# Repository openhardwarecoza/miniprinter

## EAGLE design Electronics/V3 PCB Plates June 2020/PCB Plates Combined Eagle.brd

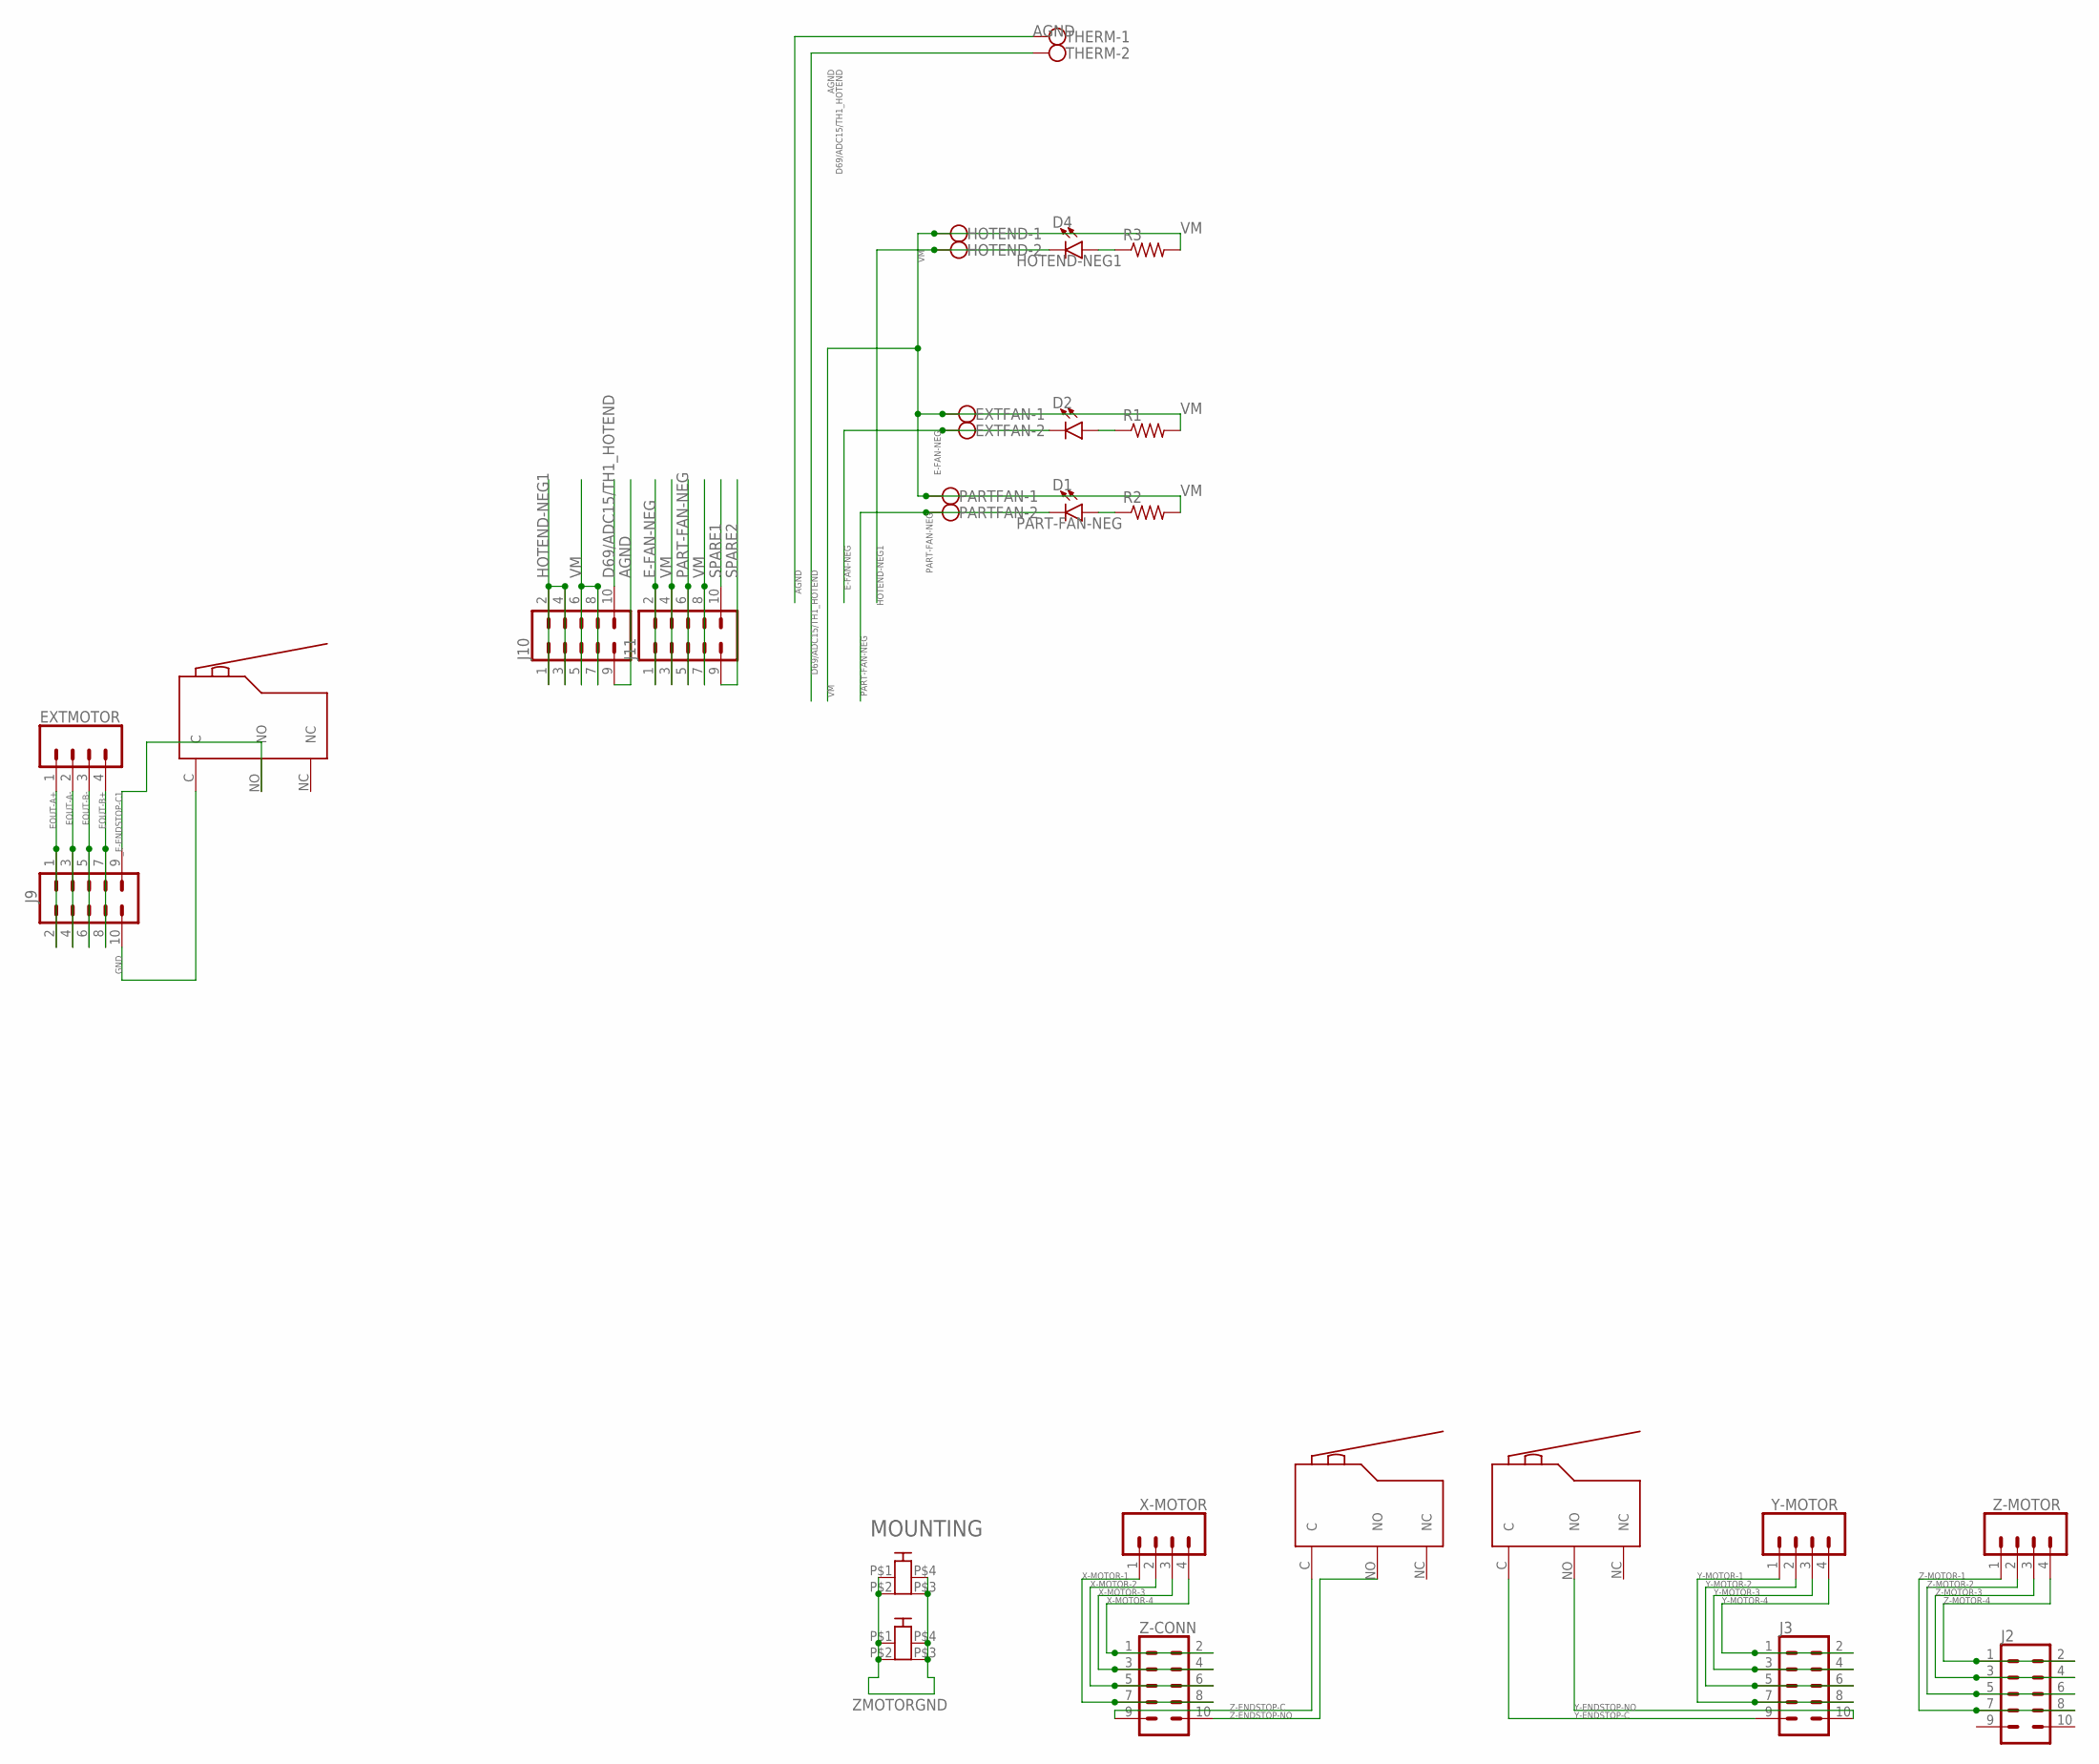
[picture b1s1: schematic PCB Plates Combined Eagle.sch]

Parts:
CON1, CON7: PCB-2M3; PCB2-M3
D1, D2, D4: LED-FKIT-1206; FKIT-LED-1206
EXTFAN: W237-102
EXTMOTOR: CONN_04SCREW_LOCK; SCREWTERMINAL-3.5MM-4_LOCK
HOTEND: W237-102
J2, J3, J9, J10, J11: CONN_05X2SHD_LOCK; 2X5-SHROUDED_LOCK
PARTFAN: W237-102
R1, R2, R3: R-US_R1206; R1206
THERM: W237-102
U$1: Lever Microswitch Leftangle PCB mount, with Rolle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; LEVERMICROPCB-LEFTANGLE
X-MOTOR: CONN_04SCREW_LOCK; SCREWTERMINAL-3.5MM-4_LOCK
XENDSTOP: Lever Microswitch Leftangle PCB mount, with Rolle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; LEVERMICROPCB-LEFTANGLE
Y-MOTOR: CONN_04SCREW_LOCK; SCREWTERMINAL-3.5MM-4_LOCK
Z-CONN: CONN_05X2SHD_LOCK; 2X5-SHROUDED_LOCK
Z-MOTOR: CONN_04SCREW_LOCK; SCREWTERMINAL-3.5MM-4_LOCK
ZENDSTOP: Lever Microswitch Leftangle PCB mount, with Rolle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; LEVERMICROPCB-LEFTANGLE

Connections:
AGND: J10.9, THERM.1
D69/ADC15/TH1_HOTEND: J10.10, THERM.2
E-FAN-NEG: D2.C, EXTFAN.2, J11.1, J11.2
EOUT-A+: EXTMOTOR.1, J9.1, J9.2
EOUT-A-: EXTMOTOR.2, J9.3, J9.4
EOUT-B+: EXTMOTOR.4, J9.7, J9.8
EOUT-B-: EXTMOTOR.3, J9.5, J9.6
GND: J9.10, XENDSTOP.C
HOTEND-NEG1: D4.C, HOTEND.2, J10.1, J10.2, J10.3, J10.4
unnamed: D2.A, R1.1
unnamed: D1.A, R2.1
unnamed: D4.A, R3.1
PART-FAN-NEG: D1.C, J11.5, J11.6, PARTFAN.2
SPARE1: J11.10
SPARE2: J11.9
VM: EXTFAN.1, HOTEND.1, J10.5, J10.6, J10.7, J10.8, J11.3, J11.4, J11.7, J11.8, PARTFAN.1, R1.2, R2.2, R3.2
X-MOTOR-1: X-MOTOR.1, Z-CONN.7, Z-CONN.8
X-MOTOR-2: X-MOTOR.2, Z-CONN.5, Z-CONN.6
X-MOTOR-3: X-MOTOR.3, Z-CONN.3, Z-CONN.4
X-MOTOR-4: X-MOTOR.4, Z-CONN.1, Z-CONN.2
Y-ENDSTOP-C: J3.9, U$1.C
Y-ENDSTOP-NO: J3.10, U$1.NO
Y-MOTOR-1: J3.7, J3.8, Y-MOTOR.1
Y-MOTOR-2: J3.5, J3.6, Y-MOTOR.2
Y-MOTOR-3: J3.3, J3.4, Y-MOTOR.3
Y-MOTOR-4: J3.1, J3.2, Y-MOTOR.4
Z-ENDSTOP-C: Z-CONN.9, ZENDSTOP.C
Z-ENDSTOP-NO: Z-CONN.10, ZENDSTOP.NO
Z-MOTOR-1: J2.7, J2.8, Z-MOTOR.1
Z-MOTOR-2: J2.5, J2.6, Z-MOTOR.2
Z-MOTOR-3: J2.3, J2.4, Z-MOTOR.3
Z-MOTOR-4: J2.1, J2.2, Z-MOTOR.4
ZMOTORGND: CON1.P$1, CON1.P$2, CON1.P$3, CON1.P$4, CON7.P$1, CON7.P$2, CON7.P$3, CON7.P$4
_E-ENDSTOP-C1: J9.9, XENDSTOP.NO

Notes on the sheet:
MOUNTING

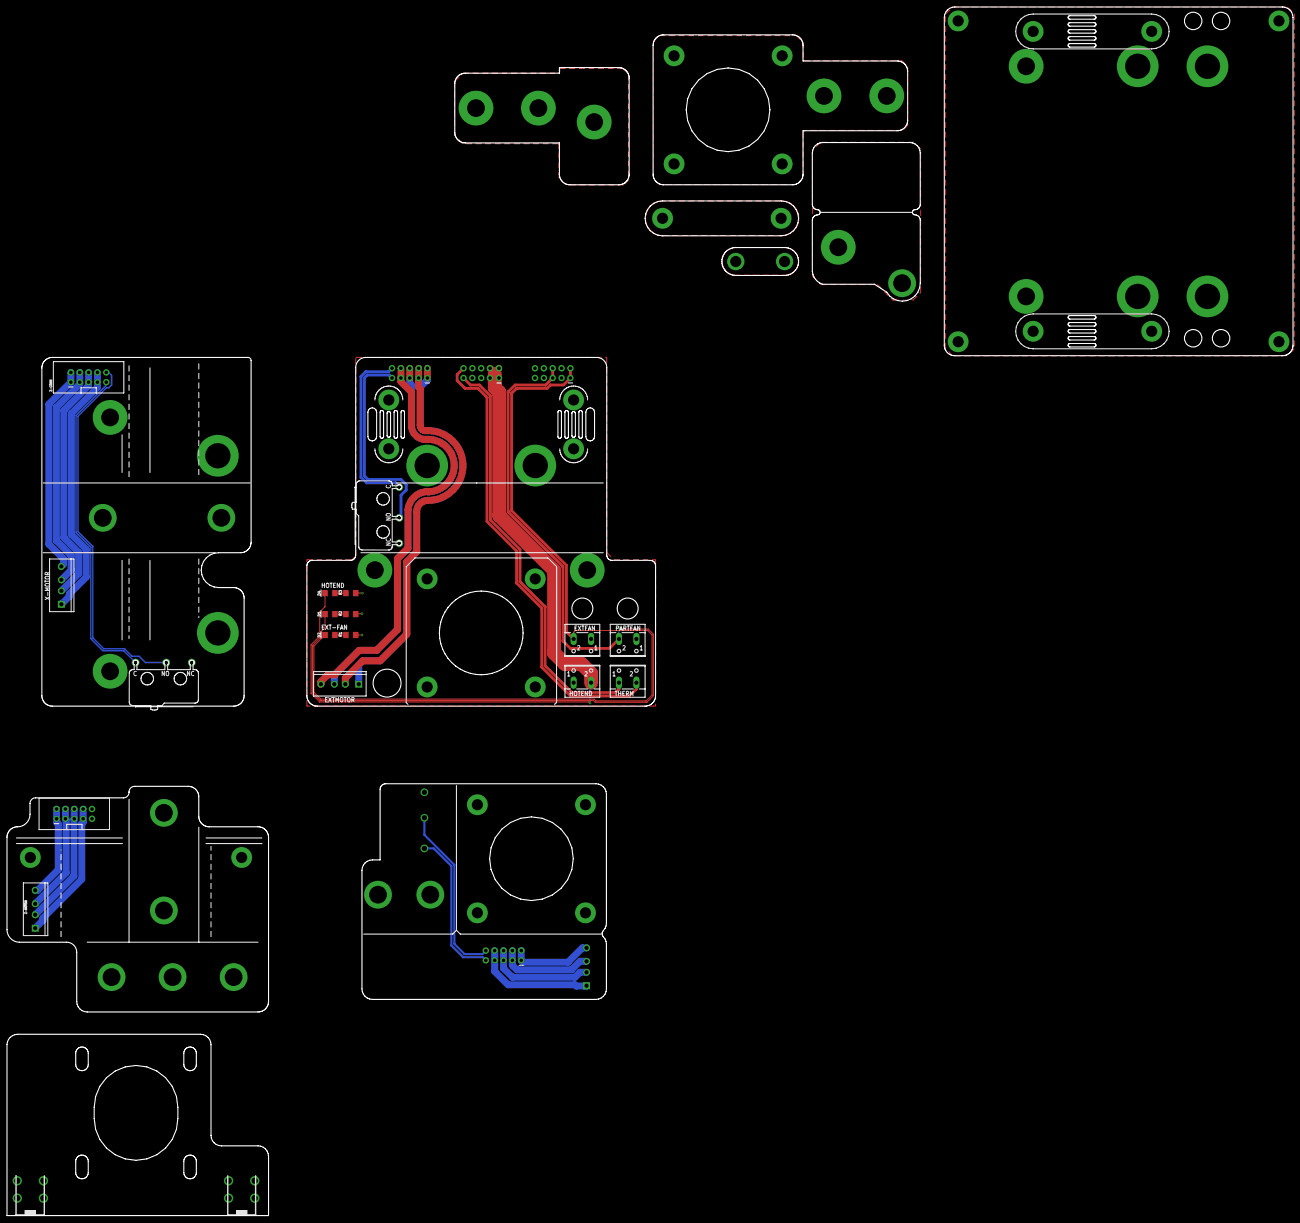
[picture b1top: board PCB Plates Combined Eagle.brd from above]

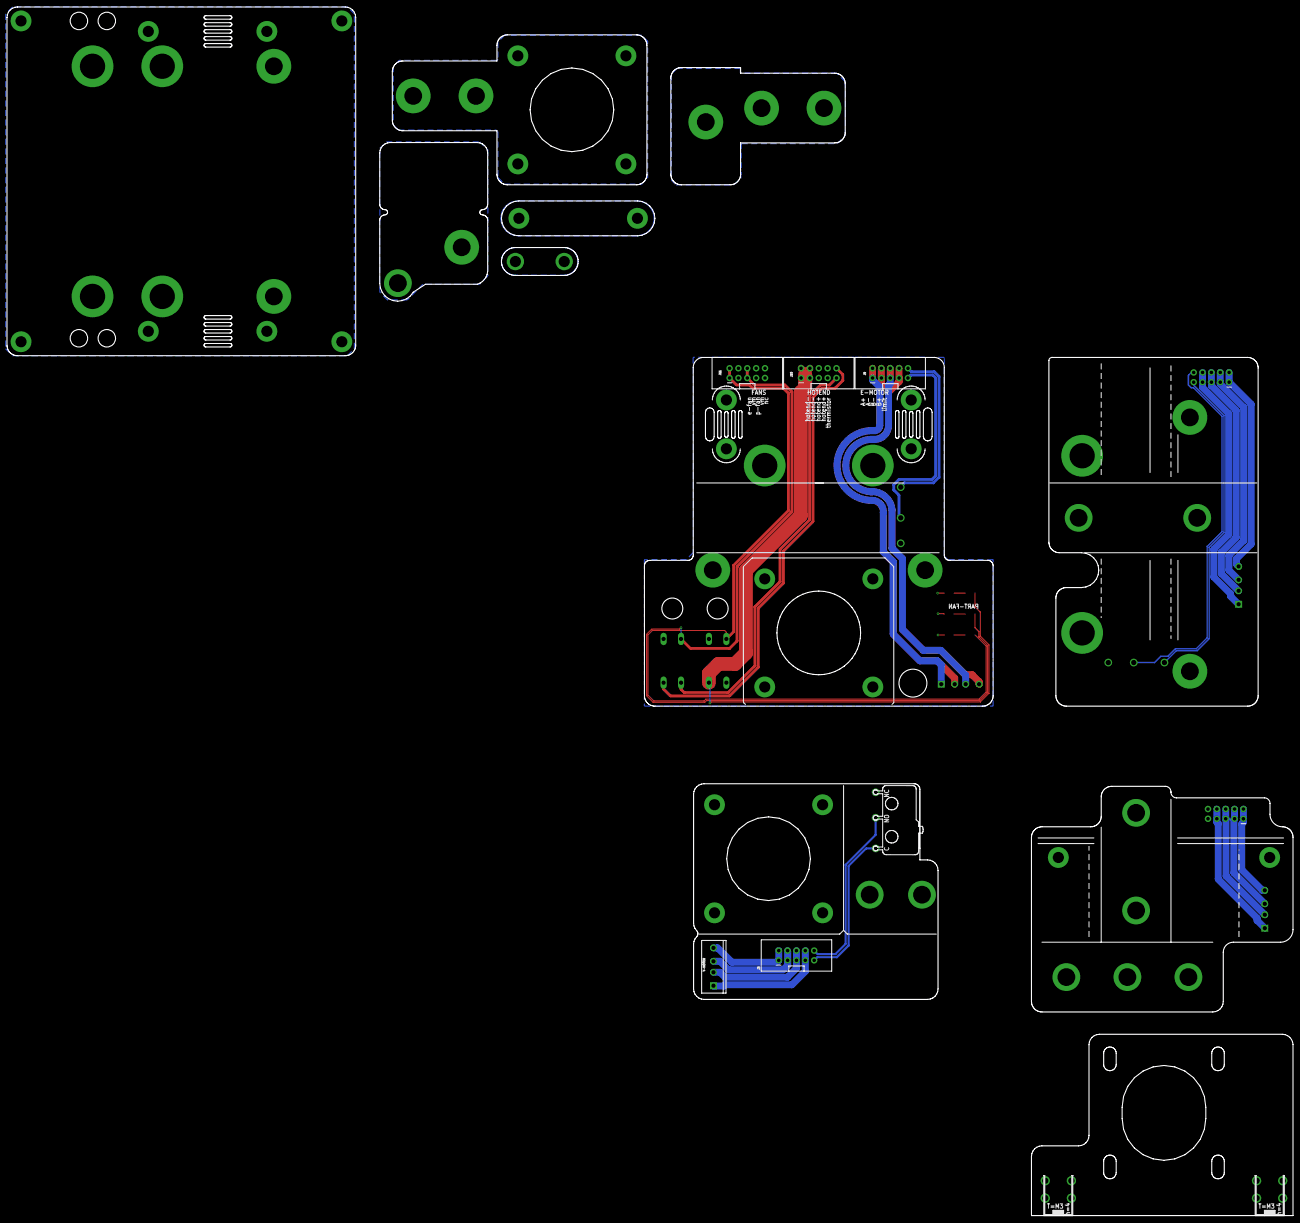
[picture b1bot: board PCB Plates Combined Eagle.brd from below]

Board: 2 copper layers, 368.8 x 346.6 mm, 25 parts (8 on the bottom side), 32 nets.

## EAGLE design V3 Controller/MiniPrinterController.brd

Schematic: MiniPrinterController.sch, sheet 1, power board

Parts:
BED: Phoenix Pluggable 5.08mm 2 way; MSTBA2
BEDTH: Phoenix Pluggable 3.81mm 2 way; MC1.5/2-G-3.81
C1, C2, C40, C41, C42, C56: 220µF 50V; E3,5-10
C3, C4, C32, C35, C37, C38, C39, C48: 10uF 50V; EIA3216
C5, C6, C7, C8, C28, C29: 100n; C0603-ROUND
C9, C10, C11, C15, C16, C19, C20, C21, C22, C24, C25, C26, C27, C34: 0.1u; C0603K
C12, C18, C23, C33: 270pF; C0603K
C13, C17: 0.1uf; C0603K
C14, C31, C36: 22p; C0603-ROUND
C30: 100n; C0603
C43, C45, C49, C50: 0.1uF; 0603-CAP
C44, C47, C51, C52: 10uF; EIA3216
C46: 0.1uF; C0603-ROUND
D1, D4, D5, D6, D7, D8, D9, D10: SMAJ90CA; DO-214AC
D2, D3, D12, D13, D16, D17, D19, D20: M4; DO-214AC
D11, D15, D18: SS34; DO-214AC
D14: SA24CA; C4111-15
D21: RED/GRN BICOLOR 3528 LED; 3528
ETHERM: Phoenix Pluggable 3.81mm 2 way; MC1.5/2-G-3.81
IC1: 4050D; SO16
IC2: 1117-33; SOT223
IC3: ATMEGA2560-16AU; TQFP100
IC5: LM358D; SO08
IC9: XL1509-5.0E1; SO08
ICSP: ICSP; 2X03
J1, J2, J6, J7, J8: CONN_05X2SHD_LOCK; 2X5-SHROUDED_LOCK
J3: USB-C-Socket; USB-C-16P
JP5, JP6: PINHD-1X1; 1X01
L: YELLOW; CHIP-LED0805
L1, L3: 39nH; 0603
L2: 68uH; CD75
LED1, LED2, LED3, LED4: 0802 SIDE EMITTING LED RED; CHIPLED_0805
LED6: 0802 SIDE EMITTING LED GREEN; LED3MM
MOS2: IRLR024; D2PACK
ON: GREEN; CHIP-LED0805
PWRIN: Phoenix Pluggable 5.08mm 2 way; MSTBA2
Q1, Q2, Q22: IRLR024; D-PAK_TO252AA
Q3: 16MHz; QS
R1, R5, R7, R17: 3K6; R0603
R2: 4K7; R0603
R3, R4, R20, R21: 10K; B25P
R6, R8, R9, R13, R14, R15, R16, R29, R33, R34, R36, R37, R38, R42, R43, R45, R46, R47, R51, R52, R61, R64, R65, R66, R67: 10k; R0603
R10, R11, R30, R31, R39, R40, R48, R49: 0.22R 3212; R1210
R12, R32, R41, R50: 6K8; R0603
R18, R19, R22, R23: 5K1; R0603
R24: 10r; R0603
R25, R44, R53, R63: 100k; R0603
R26, R27: 4k7; R0603
R28, R35: 10R; R0603@1
R54: 27R; R0603-ROUND
R55, R60, R68, R69: 1k; R0603
R56, R57, R58, R59: 330; 0603-RES
R62: 10R; R0603
R70, R71: 5.1k; 0603@1
R72, R73: 1K; 0603-RES
R74, R75, R76, R77: 1K; R0603
R78, R79, R80, R81: 10K; R0603
RESET: TS42
SJ1, SJ2, SJ3, SJ4, SJ5, SJ6, SJ7, SJ8: SJ
T2: FDN340P; SOT-23
U1: TLP291-4; SO16_TOS
U2: USD-SOCKETUSD; USD-SOCKET-PP
U6: FT232RLSSOP; SSOP28DB
U$1, U$2, U$7, U$17: TB67S109AFNG; TB67S109AFTG-HTSSPO48-P-300-0.50
U$4: ATQ-FUSE
X-END1, X-END2, X-END3: Phoenix Pluggable 3.81mm 2 way; MC1.5/2-G-3.81
Z-CONN1: CONN_05X2SHD_LOCK; 2X5-SHROUDED_LOCK

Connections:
3VUSB: C45.1, U6.17 (3V3OUT)
5VREG: C6.1, C7.1, C8.1, C9.1, C15.1, C20.1, C25.1, C30.2, C51.A (+), C56.+, IC2.3 (IN), IC3.10 (VCC), IC3.31 (VCC1), IC3.61 (VCC2), IC3.80 (VCC3), IC3.100 (AVCC), IC5.8 (V+), IC9.3 (FB), ICSP.2, JP6.1, L1.2, L2.1, LED1.C, LED2.C, LED3.C, LED4.C, R6.2, R8.2, R9.2, R12.2, R13.2, R14.2, R15.2, R16.2, R18.2, R19.2, R22.2, R23.2, R29.2, R32.2, R33.2, R34.2, R36.2, R37.2, R38.2, R41.2, R42.2, R43.2, R45.2, R46.2, R47.2, R50.2, R51.2, R52.2, R60.1, R61.2, R64.2, R65.2, R74.1, R75.1, R76.1, R77.1, R78.2, R79.2, R80.2, R81.2, T2.2 (S); also elsewhere on the board
+3V3: C28.2, C47.A (+), C49.1, C50.1, C52.A (+), IC1.1 (VDD), IC2.4 (OUT), IC5.6 (-IN), U2.4 (VCC)
AGND: BEDTH.1, C3.C (-), C4.C (-), ETHERM.1, J1.9, L3.1
AREF: C5.1, IC3.98 (AREF)
AVCC: L1.1, R26.1, R27.1
BED-NEG1: BED.1, D2.A, MOS2.2 (D)
CC1: J3.A5 (CC1), R71.2
CC2: J3.B5 (CC2), R70.2
CMP: C29.2, IC5.5 (+IN), R66.1, R67.2
CS: IC1.2 (O), U2.2 (CS)
CTS: U6.11 (CTS)
D0: IC3.2 ((RXD0/PCIN8)PE0), R68.2
D1: IC3.3 ((TXD0)PE1), R69.2
D2/EENABLE: IC3.6 ((OC3B/INT4)PE4), U$7.ENABLE
D3: IC3.7 ((OC3C/INT5)PE5), R78.1, U1.16
D4/EDIR: IC3.1 ((OC0B)PG5), U$7.CS/CCW (CW/CCW)
D5/ESTEP: IC3.5 ((OC3A/AIN1)PE3), U$7.CLK
D6: IC3.8 ((T3/INT6)PE6)
D7: IC3.9 ((CLKO/ICP3/INT7)PE7)
D8: IC3.17 (PH5(OC4C)), R79.1, U1.14
D9: IC3.18 (PH6(OC2B)), R80.1, U1.12
D10: IC3.23 ((OC2A/PCINT4)PB4), R81.1, U1.10
D11: IC3.24 ((OC1A/PCINT5)PB5)
D12: IC3.25 ((OC1B/PCINT6)PB6)
D13: IC3.26 ((OC0A/OC1C/PCINT7)PB7), R55.1
D14/TXD3: IC3.64 (PJ1(TXD3/PCINT10))
D15/RXD3: IC3.63 (PJ0(RXD3/PCINT9))
D16/TXD2: IC3.13 (PH1(TXD2))
D17/RXD2: IC3.12 (PH0(RXD2))
D18/TXD1: IC3.46 ((TXD1/INT3)PD3)
D19/RXD1: IC3.45 ((RXD1/INT2)PD2)
D20/SDA: IC3.44 ((SDA/INT1)PD1), R65.1
D21/SCL: IC3.43 ((SCL/INT0)PD0), R64.1
D22: IC3.78 ((AD0)PA0)
D23: IC3.77 ((AD1)PA1)
D24: IC3.76 ((AD2)PA2)
D25: IC3.75 ((AD3)PA3)
D26: IC3.74 ((AD4)PA4)
D27: IC3.73 ((AD5)PA5)
D28: IC3.72 ((AD6)PA6)
D29: IC3.71 ((AD7)PA7)
D30: IC3.60 ((A15)PC7)
D31: IC3.59 ((A14)PC6)
D32: IC3.58 ((A13)PC5)
D33: IC3.57 ((A12)PC4)
D34: IC3.56 ((A11)PC3)
D35: IC3.55 ((A10)PC2)
D36: IC3.54 ((A9)PC1)
D37: IC3.53 ((A8)PC0)
D38: IC3.50 ((T0)PD7)
D39: IC3.70 ((ALE)PG2)
D40: IC3.52 ((RD)PG1)
D41: IC3.51 ((WR)PG0)
D42: IC3.42 (PL7)
D43: IC3.41 (PL6)
D44: IC3.40 (PL5(OC5C))
D45: IC3.39 (PL4(OC5B))
D46: IC3.38 (PL3(OC5A))
D47: IC3.37 (PL2(T5))
D48: IC3.36 (PL1(ICP5))
D49: IC3.35 (PL0(ICP4))
D50/MISO: IC3.22 ((MISO/PCINT3)PB3), ICSP.1, U2.7 (DO)
D51/MOSI: IC1.5 (I), IC3.21 ((MOSI/PCINT2)PB2), ICSP.4
D52/SCK: IC1.7 (I), IC3.20 ((SCK/PCINT1)PB1), ICSP.3
D53/SS: IC1.3 (I), IC3.19 ((SS/PCINT0)PB0)
D54/ADC0: IC3.97 ((ADC0)PF0)
D55/ADC1/ZENABLE: IC3.96 ((ADC1)PF1), U$2.ENABLE
D56/ADC2/ZSTEP: IC3.95 ((ADC2)PF2), U$2.CLK
D57/ADC3/ZDIR: IC3.94 ((ADC3)PF3), U$2.CS/CCW (CW/CCW)
D58/ADC4/YENABLE: IC3.93 ((ADC4/TCK)PF4), U$1.ENABLE
D59/ADC5/YSTEP: IC3.92 ((ADC5/TMS)PF5), U$1.CLK
D60/ADC6/YDIR: IC3.91 ((ADC6/TDO)PF6), U$1.CS/CCW (CW/CCW)
D61/ADC7/XENABLE: IC3.90 ((ADC7/TDI)PF7), U$17.ENABLE
D62/ADC8/XSTEP: IC3.89 (PK0(ADC8/PCINT16)), U$17.CLK
D63/ADC9/XDIR: IC3.88 (PK1(ADC9/PCINT17)), U$17.CS/CCW (CW/CCW)
D64/ADC10/BED: IC3.87 (PK2(ADC10/PCINT18)), R24.1
D65/ADC11/HOTEND: IC3.86 (PK3(ADC11/PCINT19)), R62.1
D66/ADC12/E-FAN: IC3.85 (PK4(ADC12/PCINT20)), R35.2
D67/ADC13: IC3.84 (PK5(ADC13/PCINT21)), R28.2
D68/ADC14/TH2_BED: BEDTH.2, C4.A (+), IC3.83 (PK6(ADC14/PCINT22)), R27.2
D69/ADC15/TH1_HOTEND: C3.A (+), ETHERM.2, IC3.82 (PK7(ADC15/PCINT23)), J1.10, R26.2
D+1: J3.A6 (D+), J3.B6 (D+), U6.15 (USBDP)
D-1: J3.A7 (D-), J3.B7 (D-), U6.16 (USBDM)
DI: IC1.4 (O), U2.3 (DI)
DTR: C46.1, U6.2 (DTR)
E-FAN-NEG: D13.A, J2.1, J2.2, Q1.4 (D), X-END3.1
EMODE0: R45.1, U$7.DMODE0
EMODE1: R46.1, SJ5.2, U$7.DMODE1
EMODE2: R47.1, SJ6.2, U$7.DMODE2
EOUT-A+: D9.C, J7.1, J7.2, U$7.OUTA+1, U$7.OUTA+2
EOUT-A-: D9.A, J7.3, J7.4, U$7.OUTA-1, U$7.OUTA-2
EOUT-B+: D10.A, J7.7, J7.8, U$7.OUTB+1, U$7.OUTB+2
EOUT-B-: D10.C, J7.5, J7.6, U$7.OUTB-1, U$7.OUTB-2
GATE_CMD: IC5.7 (OUT), T2.3 (G)
GND: C1.-, C2.-, C5.2, C6.2, C7.2, C8.2, C9.2, C10.2, C11.2, C12.2, C13.2, C14.2, C15.2, C16.2, C17.2, C18.2, C19.2, C20.2, C21.2, C22.2, C23.2, C24.2, C25.2, C26.2, C27.2, C28.1, C29.1, C30.1, C31.1, C32.C (-), C33.2, C34.2, C35.C (-), C36.1, C37.C (-), C38.C (-), C39.C (-), C40.-, C41.-, C42.-, C43.2, C44.C (-), C45.2, C47.C (-), C48.C (-), C49.2, C50.2, C51.C (-), C52.C (-), C56.-, D14.A, D18.2 (A), IC1.8 (VSS), IC2.1 (ADJ), IC3.11 (GND), IC3.32 (GND1), IC3.62 (GND2), IC3.81 (GND3), IC3.99 (AGND), IC5.2 (-IN), IC5.3 (+IN), IC5.4 (V-), IC9.4 (EN), IC9.5 (GND1), IC9.6 (GND2), IC9.7 (GND3), IC9.8 (GND4), ICSP.6, J3.GND, J3.GND2 (GND), J6.10, J7.10, J8.10, L.C, L3.2, MOS2.3 (S), ON.C, ON.K, PWRIN.1, Q1.3 (S), Q2.3 (S), Q22.3 (S), R1.1, R2.1, R5.1, R7.1, R17.1, R25.1, R44.1, R53.1, R63.1, R67.1, R70.1, R71.1, RESET.1, RESET.2, SJ1.1, SJ2.1, SJ3.1, SJ4.1, SJ5.1, SJ6.1, SJ7.1, SJ8.1, U1.9, U1.11, U1.13, U1.15, U2.6 (GND), U2.GND1 (SHIELD), U2.GND2 (SHIELD), U6.7 (GND7), U6.18 (GND18), U6.21 (GND21), U6.25 (AGND), U6.26 (TEST), U$1.GND (GND1), U$1.GND2, U$1.GND3, U$1.GND4, U$1.GND5, U$1.GND6, U$1.GND-PAD (GNDPAD), U$2.GND (GND1), U$2.GND2, U$2.GND3, U$2.GND4, U$2.GND5, U$2.GND6, U$2.GND-PAD (GNDPAD), U$7.GND (GND1), U$7.GND2, U$7.GND3, U$7.GND4, U$7.GND5, U$7.GND6, U$7.GND-PAD (GNDPAD), U$17.GND (GND1), U$17.GND2, U$17.GND3, U$17.GND4, U$17.GND5, U$17.GND6, U$17.GND-PAD (GNDPAD), Z-CONN1.10; also elsewhere on the board
HOTEND-NEG1: D3.A, J1.1, J1.2, J1.3, J1.4, Q2.4 (D), X-END1.1
M8RXD: R68.1, U6.1 (TXD)
M8TXD: R69.1, U6.5 (RXD)
unnamed: D18.1 (C), IC9.2 (OUT), L2.2
unnamed: MOS2.1 (G), R24.2, R25.2
unnamed: Q2.1 (G), R62.2, R63.2
unnamed: D21.4 (C2), R72.2
unnamed: R1.2, R4.A
unnamed: R5.2, R20.A
unnamed: R7.2, R21.A
unnamed: R3.A, R17.2
unnamed: R3.E, R18.1
unnamed: R4.E, R19.1
unnamed: R20.E, R22.1
unnamed: R21.E, R23.1
unnamed: ON.A, R60.2
unnamed: L.A, R55.2
unnamed: LED6.K (C), R2.2
unnamed: D11.1 (C), IC9.1 (IN)
unnamed: D21.3 (C1), R73.2
unnamed: R74.2, U1.1
unnamed: R75.2, U1.3
unnamed: R76.2, U1.5
unnamed: R77.2, U1.7
unnamed: D20.A, U1.8
unnamed: D19.A, U1.6
unnamed: D17.A, U1.4
unnamed: D16.A, U1.2
unnamed: Q22.1 (G), R28.1, R44.2
unnamed: Q1.1 (G), R35.1, R53.2
P0W: C11.1, R3.S, U$17.VREFA, U$17.VREFB
P0W1: C17.1, R4.S, U$1.VREFA, U$1.VREFB
P0W2: C22.1, R20.S, U$2.VREFA, U$2.VREFB
P0W3: C27.1, R21.S, U$7.VREFA, U$7.VREFB
PART-FAN-NEG: D12.A, J2.5, J2.6, Q22.4 (D), X-END2.1
PH3: IC3.15 (PH3(OC4A))
PH4: IC3.16 (PH4(OC4B))
RESET: C14.1, C46.2, IC3.30 (RESET), ICSP.5, R61.1, RESET.3, RESET.4; also elsewhere on the board
RTS: U6.3 (RTS)
RXLED: R72.1, U6.22 (RXLED)
SC: IC1.6 (O), U2.5 (SCK)
SHLD: J3.SHLD1 (SHLD), J3.SHLD2 (SHLD), J3.SHLD3 (SHLD), J3.SHLD4 (SHLD), J3.SHLD5 (SHLD), J3.SHLD6 (SHLD), J3.SHLD7 (SHLD), J3.SHLD8 (SHLD)
SPARE1: J2.10
SPARE2: J2.9
TXLED: R73.1, U6.23 (TXLED)
V+PSU: PWRIN.2, U$4.TERM1.1, U$4.TERM1.2
V_USB: C43.1, C44.A (+), D15.2 (A), D21.1 (A1), D21.2 (A2), J3.VBUS1 (VBUS), J3.VBUS2 (VBUS), JP5.1, U6.4 (VCCIO), U6.20 (VCC)
V_USB_AFTERDIODE: D15.1 (C), T2.1 (D)
XFAULT: LED1.A, R56.1
XLO: R13.1, R56.2, U$17.LO
XMO: R14.1, U$17.MO
XMO1: R34.1, U$1.MO
XMO2: R43.1, U$2.MO
XMO3: R52.1, U$7.MO
XMODE0: R6.1, U$17.DMODE0
XMODE1: R8.1, SJ1.2, U$17.DMODE1
XMODE2: R9.1, SJ2.2, U$17.DMODE2
XOSCM: C12.1, R12.1, U$17.OSCM
XOSCM1: C18.1, R32.1, U$1.OSCM
XOSCM2: C23.1, R41.1, U$2.OSCM
XOSCM3: C33.1, R50.1, U$7.OSCM
XOUT-A+: D1.C, U$17.OUTA+1, U$17.OUTA+2, Z-CONN1.1, Z-CONN1.2
XOUT-A-: D1.A, U$17.OUTA-1, U$17.OUTA-2, Z-CONN1.3, Z-CONN1.4
XOUT-B+: D4.A, U$17.OUTB+1, U$17.OUTB+2, Z-CONN1.7, Z-CONN1.8
XOUT-B-: D4.C, U$17.OUTB-1, U$17.OUTB-2, Z-CONN1.5, Z-CONN1.6
XRSA: R11.1, U$17.RSA (RSA1), U$17.RSA2
XRSA1: R31.1, U$1.RSA (RSA1), U$1.RSA2
XRSB: R10.1, U$17.RSB1, U$17.RSB2
XRSB1: R30.1, U$1.RSB1, U$1.RSB2
XTAL1: C31.2, Q3.2, R54.2; also elsewhere on the board
XTAL1R: IC3.34 (XTAL1), R54.1
XTAL2: C36.2, IC3.33 (XTAL2), Q3.1; also elsewhere on the board
XVCCINT: C13.1, U$17.VCC
Y2FAULT: LED3.A, R58.1
Y2LO: R42.1, R58.2, U$2.LO
Y2RSA2: R40.1, U$2.RSA (RSA1), U$2.RSA2
Y2RSB2: R39.1, U$2.RSB1, U$2.RSB2
Y2VCCINT: C24.1, U$2.VCC
YFAULT: LED2.A, R57.1
YLO: R33.1, R57.2, U$1.LO
YMODE0: R15.1, U$1.DMODE0
YMODE1: R16.1, SJ3.2, U$1.DMODE1
YMODE2: R29.1, SJ4.2, U$1.DMODE2
YOUT-A+: D5.C, J6.1, J6.2, U$1.OUTA+1, U$1.OUTA+2
YOUT-A-: D5.A, J6.3, J6.4, U$1.OUTA-1, U$1.OUTA-2
YOUT-B+: D6.A, J6.7, J6.8, U$1.OUTB+1, U$1.OUTB+2
YOUT-B-: D6.C, J6.5, J6.6, U$1.OUTB-1, U$1.OUTB-2
YVCCINT: C19.1, U$1.VCC
ZFAULT: LED4.A, R59.1
ZLO: R51.1, R59.2, U$7.LO
ZMODE0: R36.1, U$2.DMODE0
ZMODE1: R37.1, SJ7.2, U$2.DMODE1
ZMODE2: R38.1, SJ8.2, U$2.DMODE2
ZOUT-A+: D7.C, J8.1, J8.2, U$2.OUTA+1, U$2.OUTA+2
ZOUT-A-: D7.A, J8.3, J8.4, U$2.OUTA-1, U$2.OUTA-2
ZOUT-B+: D8.A, J8.7, J8.8, U$2.OUTB+1, U$2.OUTB+2
ZOUT-B-: D8.C, J8.5, J8.6, U$2.OUTB-1, U$2.OUTB-2
ZRSA3: R49.1, U$7.RSA (RSA1), U$7.RSA2
ZRSB3: R48.1, U$7.RSB1, U$7.RSB2
ZVCCINT: C34.1, U$7.VCC
_E-ENDSTOP-C1: D20.C, J7.9
_X-ENDSTOP-C1: D16.C, Z-CONN1.9
_Y-ENDSTOP-C1: D17.C, J6.9
_Z-ENDSTOP-C1: D19.C, J8.9

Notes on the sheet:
MICROSTEP
STEPPER MOTORS
X-AXIS STEPPER DRIVER
Y-AXIS STEPPER DRIVER
Z-AXIS STEPPER DRIVER
E-AXIS STEPPER DRIVER
MICROSTEP JUMPERS
PWRIN
VIN 12-30VDC
REVERSE POLARITY PROT
SWITCH
VM CAPACITORS
PLUG
5V SWITCHMODE REGULATOR
HOTEND MOSFET
POWER
OUTPUT
DRIVERS
BED MOSFET
(SCK)
(MISO)
(MOSI)
pwm
(TX0)
(RX0)
serial in/out
USB TO SERIAL
TLP291-4

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
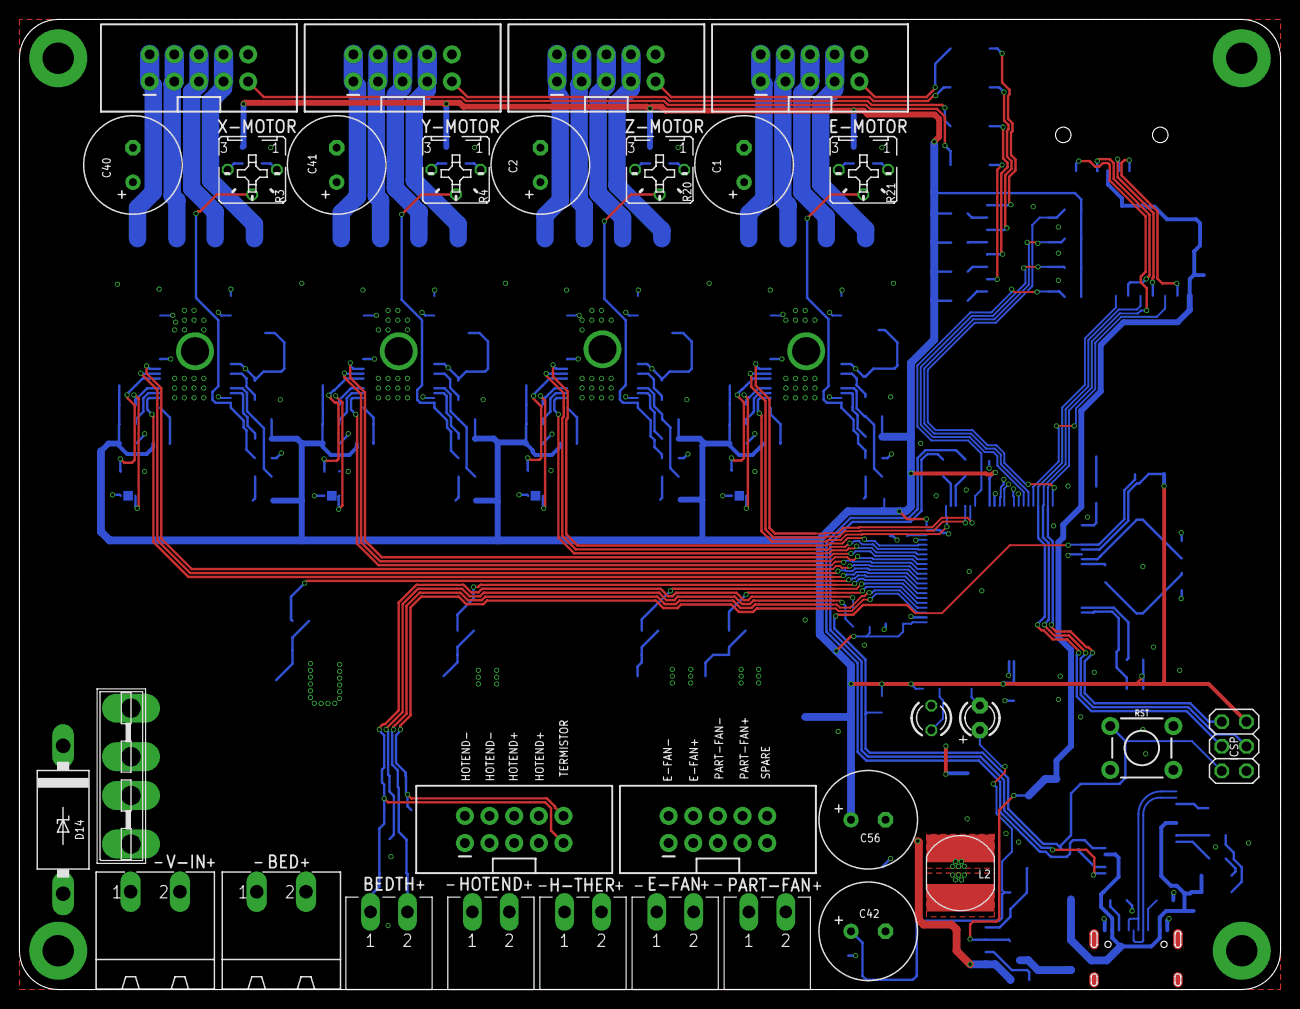
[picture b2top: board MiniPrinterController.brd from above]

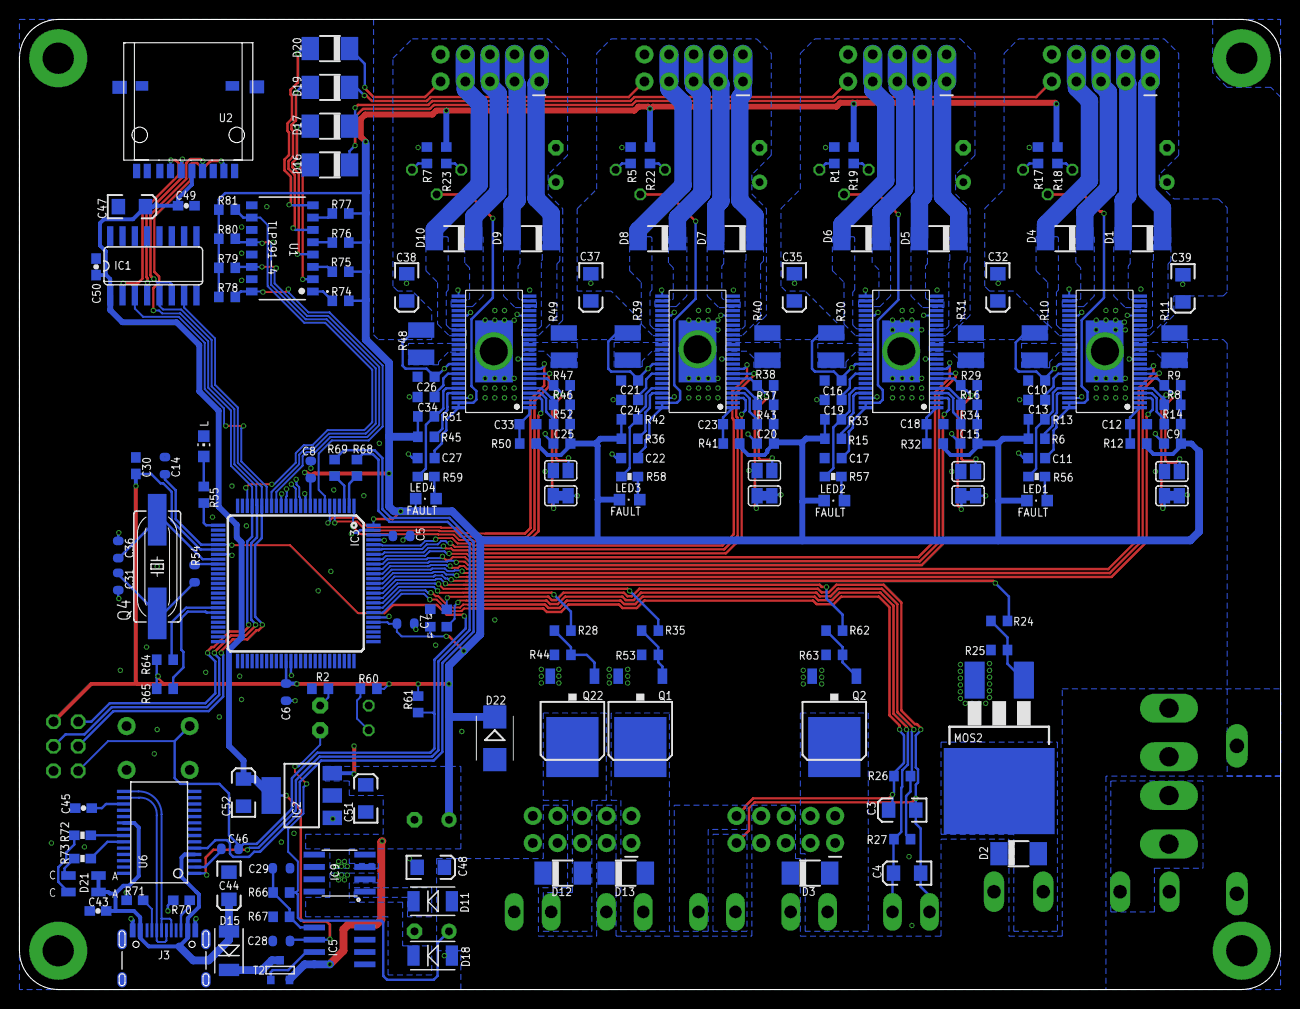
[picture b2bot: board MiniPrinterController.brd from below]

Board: 2 copper layers, 130.0 x 100.0 mm, 209 parts (179 on the bottom side), 156 nets.

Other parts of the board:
D22: 5.1V; SMB
Q4: 16Mhz; HC49UP
RST: MOMENTARY-SWITCH-SPST-PTH-6.0MM; TACTILE_SWITCH_PTH_6.0MM

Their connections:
5VREG: D22.C; also elsewhere on the board
GND: D22.A, RST.3; also elsewhere on the board
RESET: RST.1; also elsewhere on the board
XTAL1: Q4.1; also elsewhere on the board
XTAL2: Q4.2; also elsewhere on the board

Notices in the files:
parts and their libraries:
rc-master-smd: Copyright (C) 2007, Bob Starr
SparkFun-Connectors: Licensing: Creative Commons ShareAlike 4.0 International - https://creativecommons.org/licenses/by-sa/4.0
SparkFun-Resistors: Licensing: CC v3.0 Share-Alike You are welcome to use this library for commercial purposes.
